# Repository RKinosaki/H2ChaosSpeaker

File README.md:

# H2ChaosSpeaker
Speaker code for Hades 2 Chaos cosplay, equipped with a slider for volume and track control, and OLED display and buttons for control.

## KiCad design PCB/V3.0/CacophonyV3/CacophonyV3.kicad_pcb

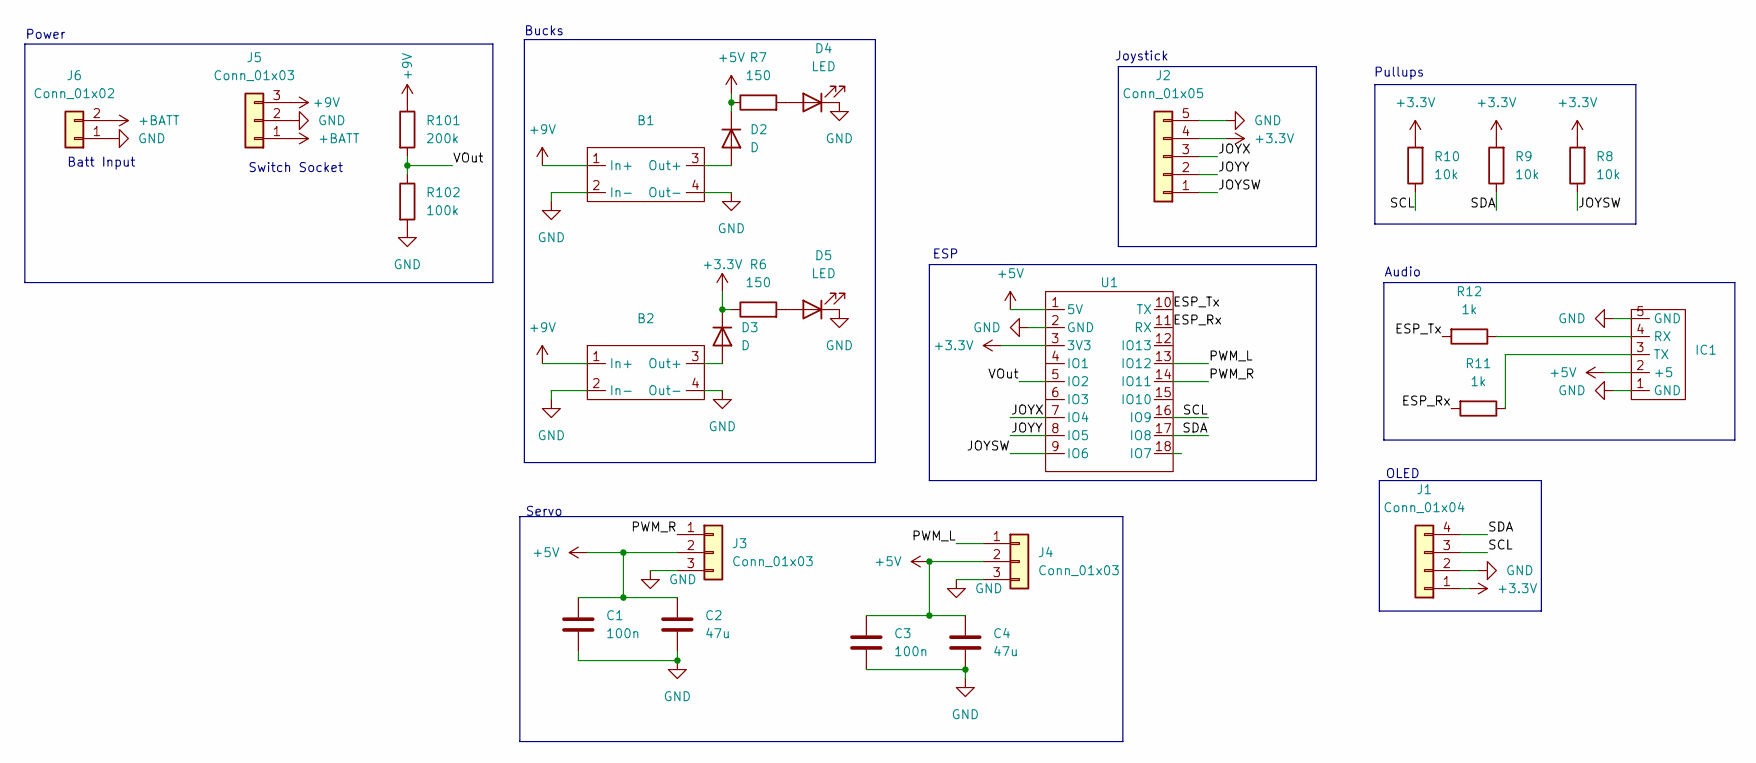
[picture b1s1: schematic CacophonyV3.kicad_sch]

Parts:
B1, B2: MiniBuck
C1, C3: 100n; R_0402_1005Metric
C2, C4: 47u; R_0402_1005Metric
D2, D3: D; D_SMA
D4, D5: LED; LED_0402_1005Metric
IC1: DYSV5W
J1: Conn_01x04; JST_XH_B4B-XH-A_1x04_P2.50mm_Vertical
J2: Conn_01x05; JST_XH_B5B-XH-A_1x05_P2.50mm_Vertical
J3, J4, J5: Conn_01x03; JST_XH_B3B-XH-A_1x03_P2.50mm_Vertical
J6: Conn_01x02; JST_XH_B2B-XH-A_1x02_P2.50mm_Vertical
R6: 150; R_0402_1005Metric
R7: 150; C_0402_1005Metric
R8, R9, R10: 10k; R_0402_1005Metric
R11, R12: 1k; R_0402_1005Metric
R101: 200k; R_0402_1005Metric
R102: 100k; R_0402_1005Metric
U1: ESP32 S3 Zero

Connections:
+3.3V: D3.1 (K), J1.1, J2.4, R6.1, R8.2, R9.2, R10.2, U1.3 (3V3)
+5V: C1.1, C2.1, C3.1, C4.1, D2.1 (K), IC1.2 (+5), J3.2, J4.2, R7.1, U1.1 (5V)
+9V: B1.1 (In+), B2.1 (In+), J5.3, R101.1
+BATT: J5.1, J6.2
/ESP_Rx: R11.2, U1.11 (RX)
/ESP_Tx: R12.2, U1.10 (TX)
/JOYSW: J2.1, R8.1, U1.9 (IO6)
/JOYX: J2.3, U1.7 (IO4)
/JOYY: J2.2, U1.8 (IO5)
/PWM_L: J4.1, U1.13 (IO12)
/PWM_R: J3.1, U1.14 (IO11)
/SCL: J1.3, R10.1, U1.16 (IO9)
/SDA: J1.4, R9.1, U1.17 (IO8)
/VOut: R101.2, R102.1, U1.5 (IO2)
GND: B1.2 (In-), B1.4 (Out-), B2.2 (In-), B2.4 (Out-), C1.2, C2.2, C3.2, C4.2, D4.1 (K), D5.1 (K), IC1.1 (GND), IC1.5 (GND), J1.2, J2.5, J3.3, J4.3, J5.2, J6.1, R102.2, U1.2 (GND)
unnamed: B1.3 (Out+), D2.2 (A)
unnamed: B2.3 (Out+), D3.2 (A)
unnamed: D4.2 (A), R7.2
unnamed: D5.2 (A), R6.2
unnamed: IC1.4 (RX), R12.1
unnamed: IC1.3 (TX), R11.1

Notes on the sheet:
Servo
ESP
Batt Input
Joystick
Switch Socket
Power
OLED
Pullups
Bucks
Audio

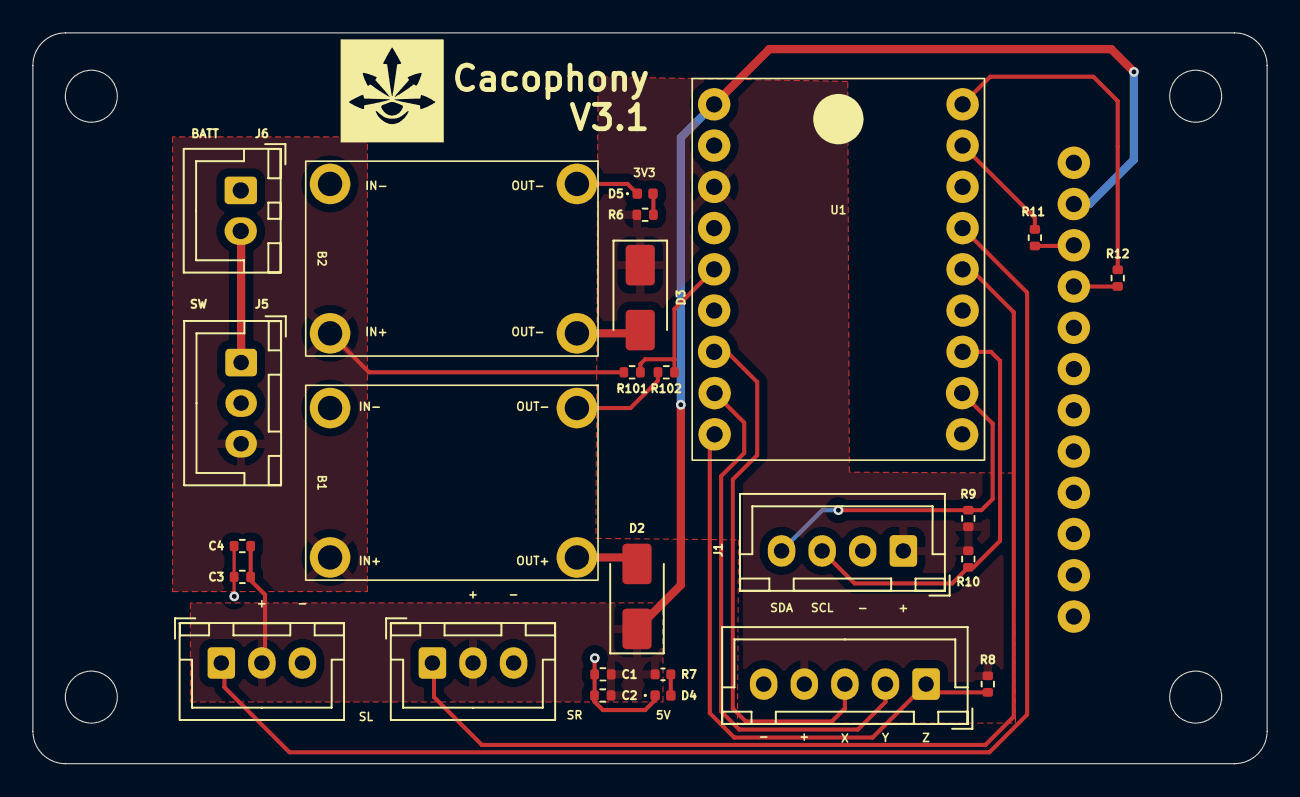
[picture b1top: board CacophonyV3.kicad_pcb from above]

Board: 2 copper layers, 76.0 x 45.0 mm, 27 parts (1 on the bottom side), 21 nets.

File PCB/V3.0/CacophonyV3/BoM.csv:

"Reference","Value","Datasheet","Footprint","Qty","DNP"
"B1,B2,IC1,U1","~","","Cacophony:DYSV5W,Cacophony:MiniBuck,ESPS3Zero:ESP32 S3 Zero","4",""
"C1,C3","100n","~","Capacitor_SMD:C_1206_3216Metric","2",""
"C2,C4","47u","~","Capacitor_SMD:C_1206_3216Metric","2",""
"D2,D3","D","~","Diode_SMD:D_SMA","2",""
"D4,D5","LED","~","LED_SMD:LED_0603_1608Metric","2",""
"J1","Conn_01x04","~","Connector_JST:JST_XH_B4B-XH-A_1x04_P2.50mm_Vertical","1",""
"J2","Conn_01x05","~","Connector_JST:JST_XH_B5B-XH-A_1x05_P2.50mm_Vertical","1",""
"J3,J4,J5","Conn_01x03","~","Connector_JST:JST_XH_B3B-XH-A_1x03_P2.50mm_Vertical","3",""
"J6","Conn_01x02","~","Connector_JST:JST_XH_B2B-XH-A_1x02_P2.50mm_Vertical","1",""
"R6,R7","150","~","Resistor_SMD:R_2512_6332Metric","2",""
"R8,R9,R10,R11,R12","10k","~","Resistor_SMD:R_2512_6332Metric","5",""

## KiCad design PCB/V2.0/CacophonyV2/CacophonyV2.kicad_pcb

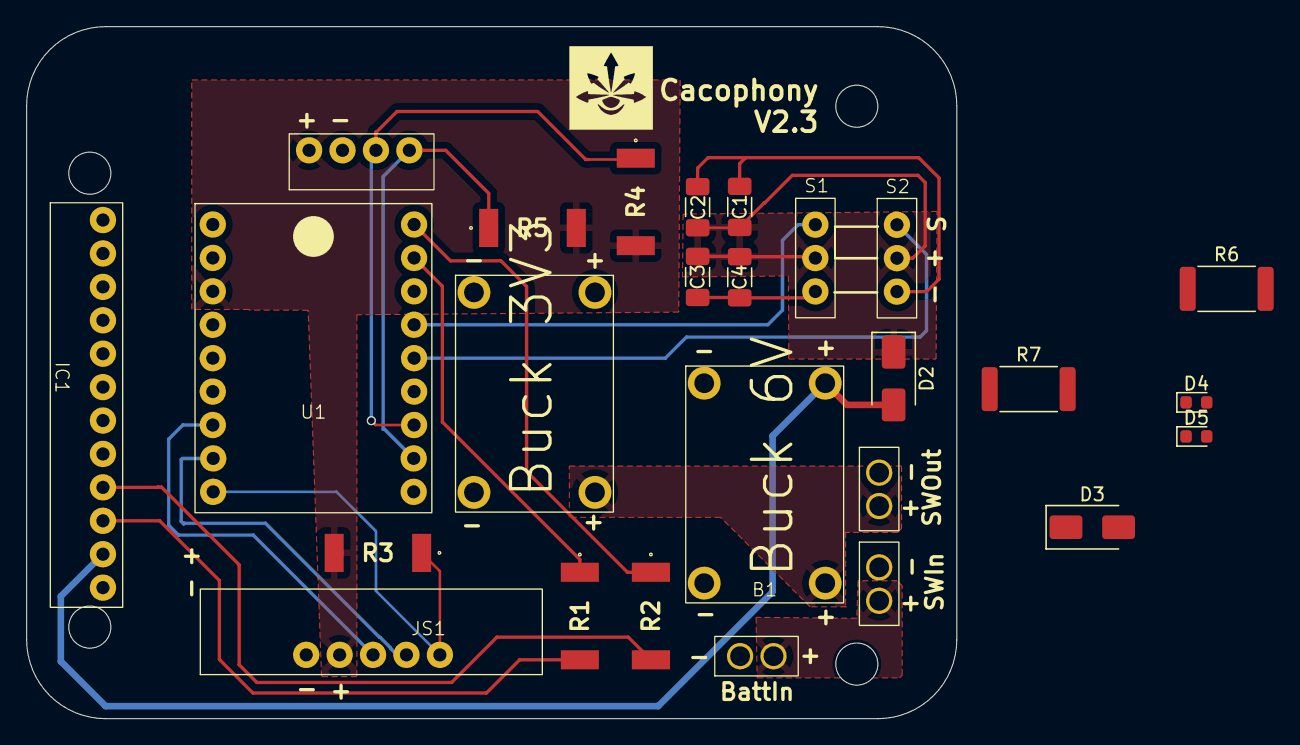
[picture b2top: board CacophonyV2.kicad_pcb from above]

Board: 2 copper layers, 70.7 x 52.6 mm, 26 parts (0 on the bottom side), 20 nets.

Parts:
B1, B2: MiniBuck
C1, C2, C3, C4: LMJ316BB7226KLHT; C_1206_3216Metric_Pad1.33x1.80mm_HandSolder
D1: I2C OLED
D2, D3: D; D_SMA
D4, D5: LED; LED_0603_1608Metric
IC1: DYSV5W
JS1: Joystick
R1, R2, R3, R4, R5: ERJ-U1TJ102U; ERJS1T_U1T__2512_
R6, R7: 150; R_2512_6332Metric
S1, S2: SG90
T1, T2, T3: MalePin_2.54_2P
U1: ESP32 S3 Zero

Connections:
+3.3V: D1.1 (Vcc), D3.1 (K), JS1.2 (+5), R3.2, R4.2, R5.2, R6.1, U1.3 (3V3)
+5V: C1.1, C2.1, C3.1, C4.1, D2.1 (K), IC1.2 (+5), R7.1, S1.2 (6V), S2.2 (6V)
+9V: B1.1 (In+), B2.1 (In+), T3.1
+BATT: T1.1, T2.1
/JOYSW: JS1.5 (SW), R3.1, U1.9 (IO6)
/JOYX: JS1.3 (VRX), U1.7 (IO4)
/JOYY: JS1.4 (VRY), U1.8 (IO5)
/PWM_L: S2.1 (PWM), U1.14 (IO11)
/PWM_R: S1.1 (PWM), U1.13 (IO12)
/SCL: D1.3 (SCK), R4.1, U1.16 (IO9)
/SDA: D1.4 (SDA), R5.1, U1.17 (IO8)
GND: B1.2 (In-), B1.4 (Out-), B2.2 (In-), B2.4 (Out-), C1.2, C2.2, C3.2, C4.2, D1.2 (GND), D4.1 (K), D5.1 (K), IC1.1 (GND), IC1.5 (GND), JS1.1 (GND), S1.3 (GND), S2.3 (GND), T1.2, T2.2, T3.2, U1.2 (GND)
unnamed: B1.3 (Out+), D2.2 (A)
unnamed: B2.3 (Out+), D3.2 (A)
unnamed: D4.2 (A), R7.2
unnamed: D5.2 (A), R6.2
unnamed: IC1.4 (RX), R2.2
unnamed: IC1.3 (TX), R1.2
unnamed: R1.1, U1.11 (RX)
unnamed: R2.1, U1.10 (TX)

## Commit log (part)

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2024-08-11 Addes code for OLED
2024-08-24 Added button inputs and slide change fixes
2024-09-18 Rename PCB_Chaos_16-09-2024.zip to ChaosSpeakerGerber.zip
2024-09-18 Create adaw
2024-09-18 Create adwad
2025-02-03 setup
2025-06-14 Added PCB
2025-07-14 Added PCBv3
2025-09-16 Fixed OLED Display
2025-09-16 Added pointer-based fsm
2025-09-17 Added menu functions
2025-09-17 Default Menu Completed
2025-09-17 New PCB
2025-09-18 PCBv3 Fabrication
2025-09-19 Added audio and volume control
2025-09-19 Added track display
2025-10-16 SImplified UI, fixed JS
2025-10-21 Servo Functional
2025-10-25 Added moving eyes
2026-01-18 Add motor test code
